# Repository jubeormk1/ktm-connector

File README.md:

# What is this?

This is a very simple design of a electric battery connector that covers the need of charging an Amparo 12Ah KTM e-bike. Given that I could not find a commercially available connector I capture the mechanical dimensions and electrical requirements to match my battery charger rating.

The design is compose of the next parts:

- Pins to match the battery connector (pure nickel 1.5mm).
- PCB that capture the position of the pins and facilitate electrical connections.
- Two part case that provides rigidity, pin short circuit protection and alignment aids.  

## Case and Pins

The case and pins have been designed using Fusion 360 and because of that it can be shared but not edited. Exported models will be available under the ''Models'' folder
- [Full Assembly](https://a360.co/49ZnHQx)
- [Battery Pin](https://a360.co/49YjsVp)

## PCB
The PCB has been designed with [KiCAD 7.0](https://www.kicad.org/) which made everything very easy.

## Thanks

Thanks to the [Hawthorn Community Connected Hacker Space (CCHS)](https://www.hackmelbourne.org/) for ideas, assistance cutting the pins and in general being a bunch of very helpful and skilled people. Thanks for the bicycle and the rework of the battery to another bunch of helpful people: [The Recycling Bicycle Shed](https://thebikeshed.org.au/) in the [Ceres Environmental Park](https://ceres.org.au/).

Also thanks [PCBWay](https://www.pcbway.com/) for sponsoring the [CCHS](https://www.hackmelbourne.org/), providing members with free PCBs. Yuhuu!.

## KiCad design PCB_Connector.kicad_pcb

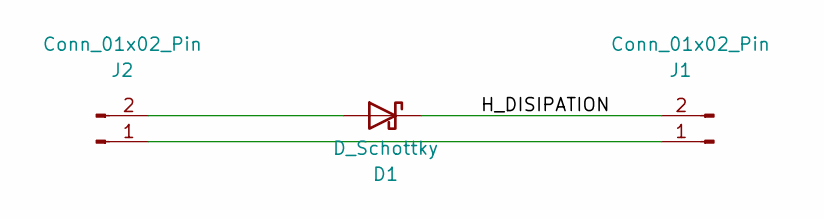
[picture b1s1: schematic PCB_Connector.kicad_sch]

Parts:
D1: D_Schottky; D_PowerDI-5
J1: Conn_01x02_Pin; KTM-Connector
J2: Conn_01x02_Pin; Big Solder Pins

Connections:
/H_DISIPATION: D1.1 (K), J1.2
unnamed: D1.2 (A), J2.2
unnamed: J1.1, J2.1

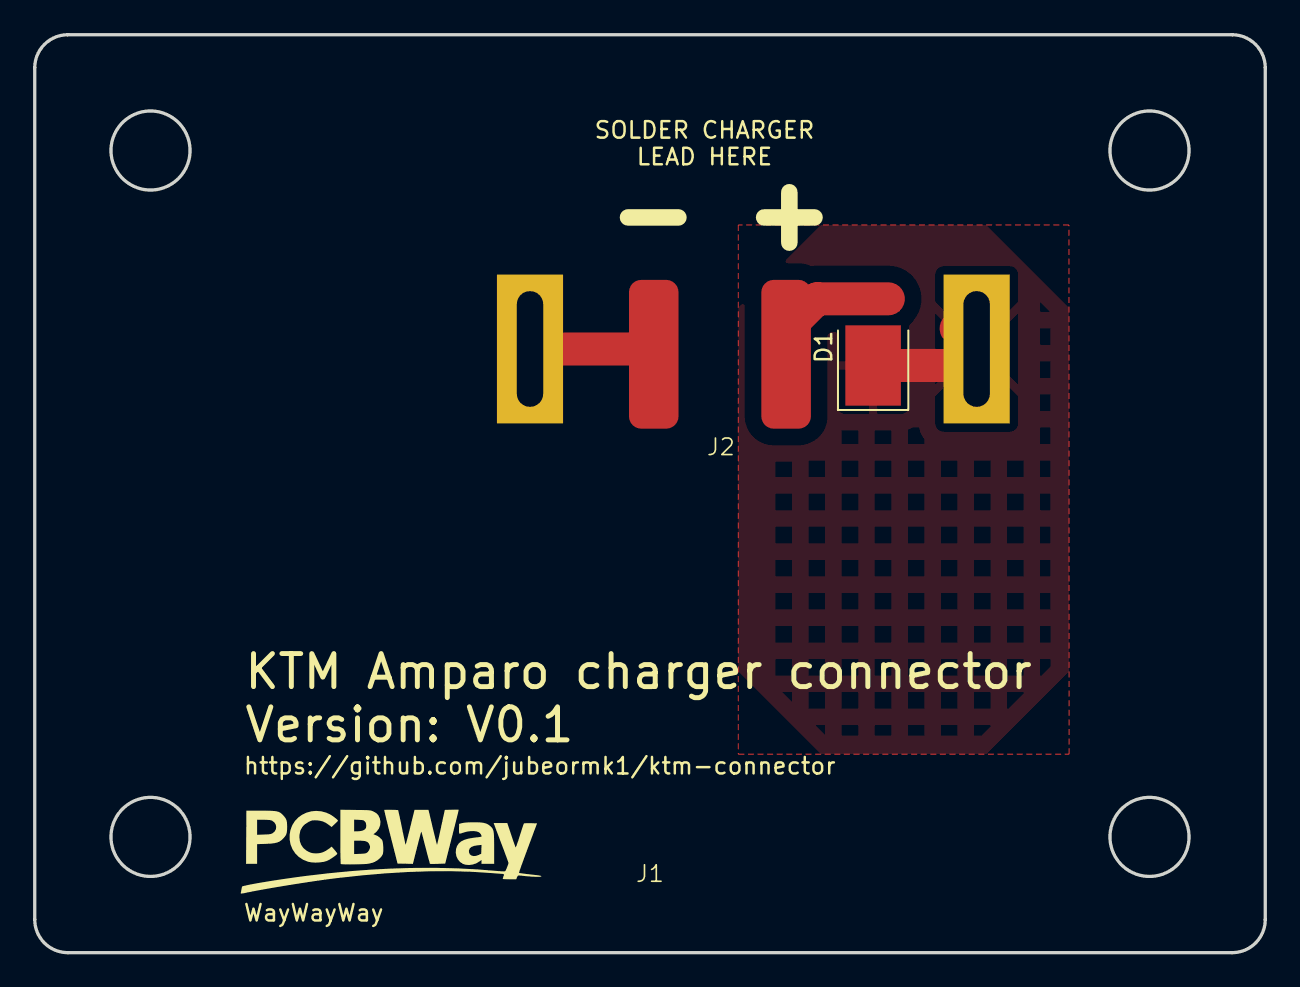
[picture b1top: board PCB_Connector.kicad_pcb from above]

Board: 2 copper layers, 74.4 x 55.5 mm, 3 parts (0 on the bottom side), 3 nets.

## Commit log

2024-03-02 WIP First Commit!
    The board has not been printed but it is dimensionally tested. At this
    stage the connector case needs to be reworked.
2024-03-02 Removing note
2024-03-02 Adding version
2024-03-02 Adding some images
2024-03-02 Removing backups
2024-03-02 Adding PCBWay for a free order :-D
2024-03-02 gnoring out
2024-03-03 Adding more marking to the PCB and updating image
2024-03-03 Update README.md
    Updating PCB Image
2024-03-03 Create LICENSE
2024-03-08 Update README.md
    Adding a section for thanks and including explicitly PCB way in the README file as requested
